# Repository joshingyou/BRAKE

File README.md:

# BRAKE
Introducing BRAKE: an integrated safety system designed for everyday bikers.

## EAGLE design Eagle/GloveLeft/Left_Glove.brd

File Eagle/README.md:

# BRAKE/Eagle
This is where the Eagle PCB design files live.

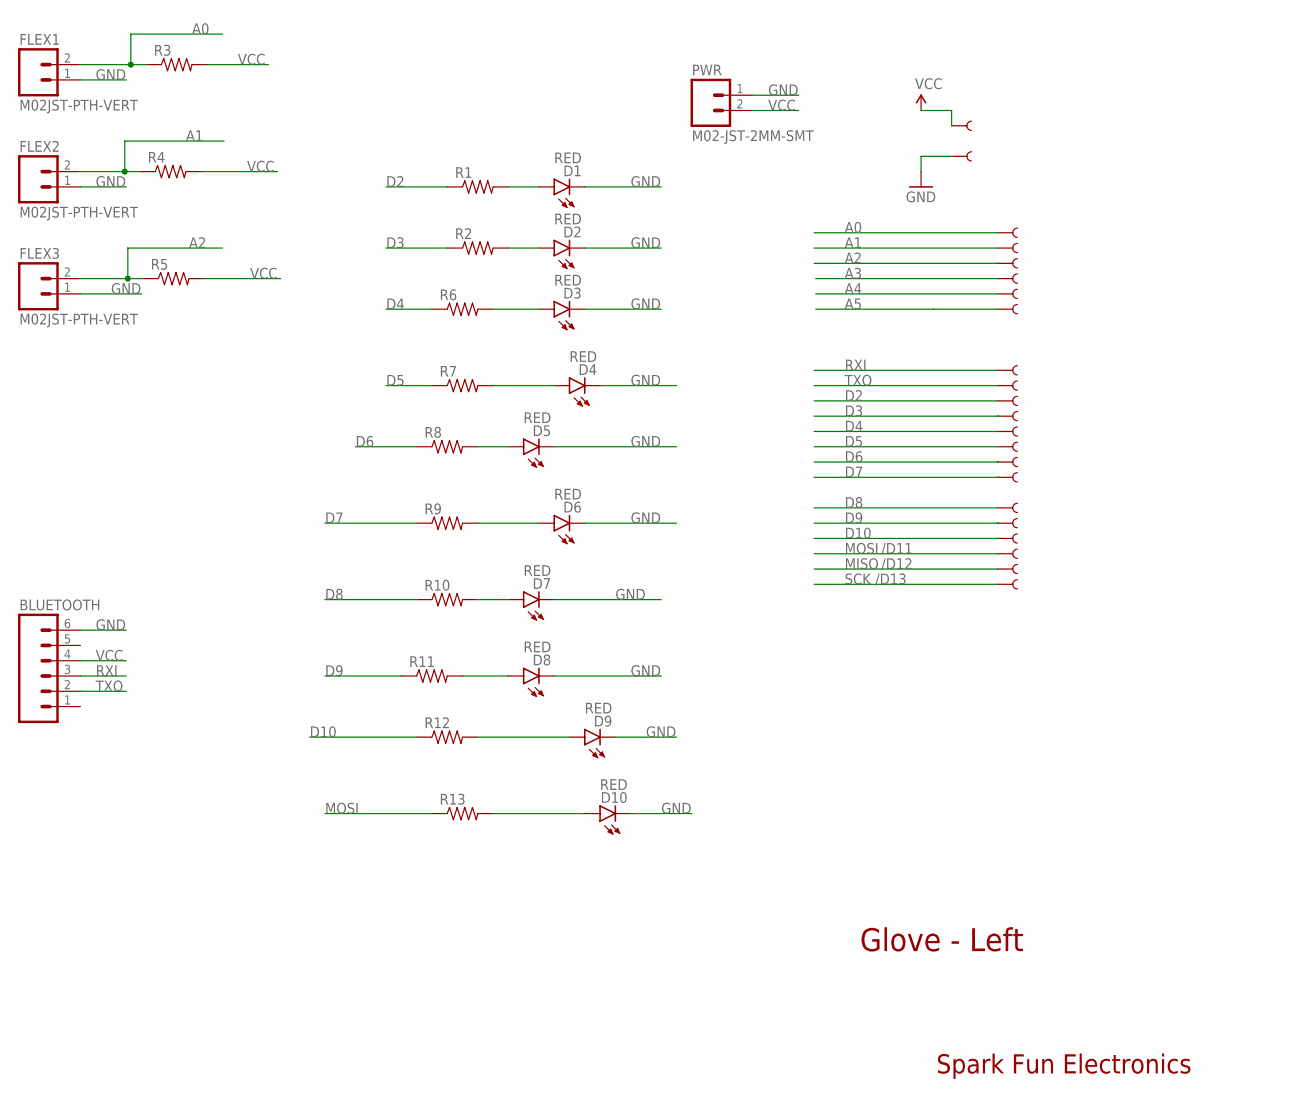
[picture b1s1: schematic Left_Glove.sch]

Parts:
BLUETOOTH: M06LOCK; 1X06_LOCK
D1, D2, D3, D4, D5, D6, D7, D8, D9, D10: RED; LED-1206
FLEX1, FLEX2, FLEX3: M02JST-PTH-VERT; JST-2-PTH-VERT
PWR: M02-JST-2MM-SMT; JST-2-SMD
R1, R2, R3, R4, R5, R6, R7, R8, R9, R10, R11, R12, R13: RESISTOR1206; 1206
U$22, U$23, U$24, U$26, U$27, U$28, U$29, U$30, U$31, U$32, U$33, U$34, U$35, U$36, U$37, U$38, U$39, U$40, U$41, U$42, U$43, U$44: SEWTAP1; PETAL-LONG-1

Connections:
A0: FLEX1.2, R3.1, U$24.P$1
A1: FLEX2.2, R4.1, U$26.P$1
A2: FLEX3.2, R5.1, U$27.P$1
A3: U$28.P$1
A4: U$29.P$1
A5: U$30.P$1
D2: R1.1, U$33.P$1
D3: R2.1, U$34.P$1
D4: R6.1, U$35.P$1
D5: R7.1, U$36.P$1
D6: R8.1, U$37.P$1
D7: R9.1, U$38.P$1
D8: R10.1, U$39.P$1
D9: R11.1, U$40.P$1
D10: R12.1, U$41.P$1
GND: BLUETOOTH.6, D1.C, D2.C, D3.C, D4.C, D5.C, D6.C, D7.C, D8.C, D9.C, D10.C, FLEX1.1, FLEX2.1, FLEX3.1, PWR.1 (2), U$23.P$1
MISO: U$43.P$1
MOSI: R13.1, U$42.P$1
unnamed: D10.A, R13.2
unnamed: D2.A, R2.2
unnamed: D1.A, R1.2
unnamed: D3.A, R6.2
unnamed: D4.A, R7.2
unnamed: D5.A, R8.2
unnamed: D6.A, R9.2
unnamed: D7.A, R10.2
unnamed: D8.A, R11.2
unnamed: D9.A, R12.2
RXI: BLUETOOTH.3, U$31.P$1
SCK: U$44.P$1
TXO: BLUETOOTH.2, U$32.P$1
VCC: BLUETOOTH.4, PWR.2 (1), R3.2, R4.2, R5.2, U$22.P$1

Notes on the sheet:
Glove - Left
Spark Fun Electronics
/D11
/D12
/D13

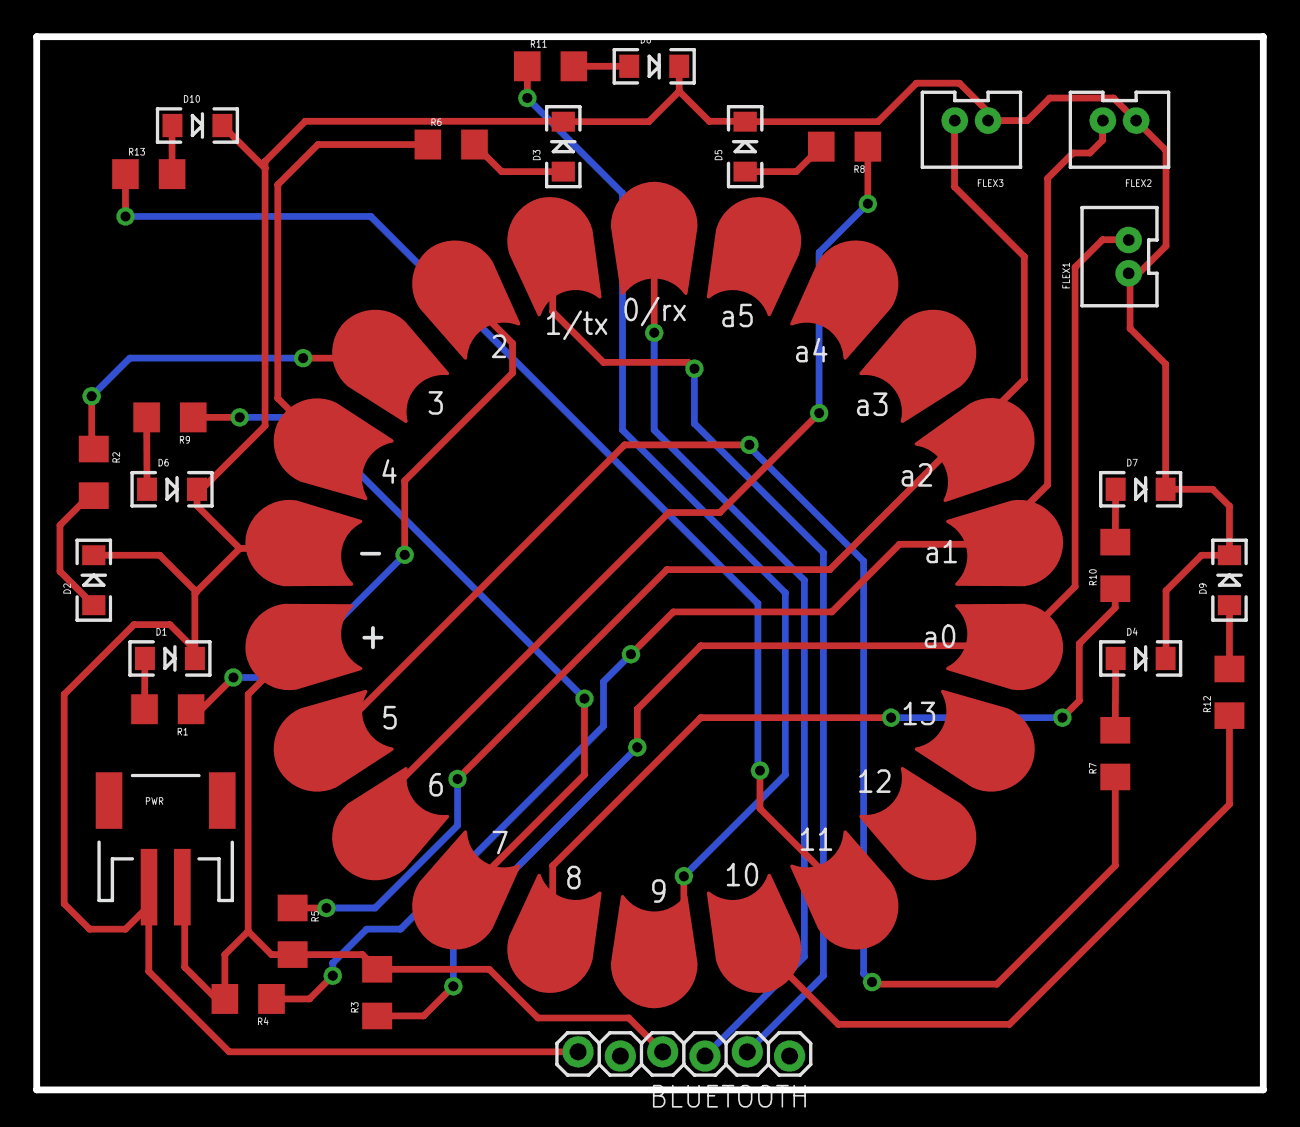
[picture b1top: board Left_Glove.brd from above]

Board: 2 copper layers, 73.7 x 63.2 mm, 50 parts (0 on the bottom side), 27 nets.

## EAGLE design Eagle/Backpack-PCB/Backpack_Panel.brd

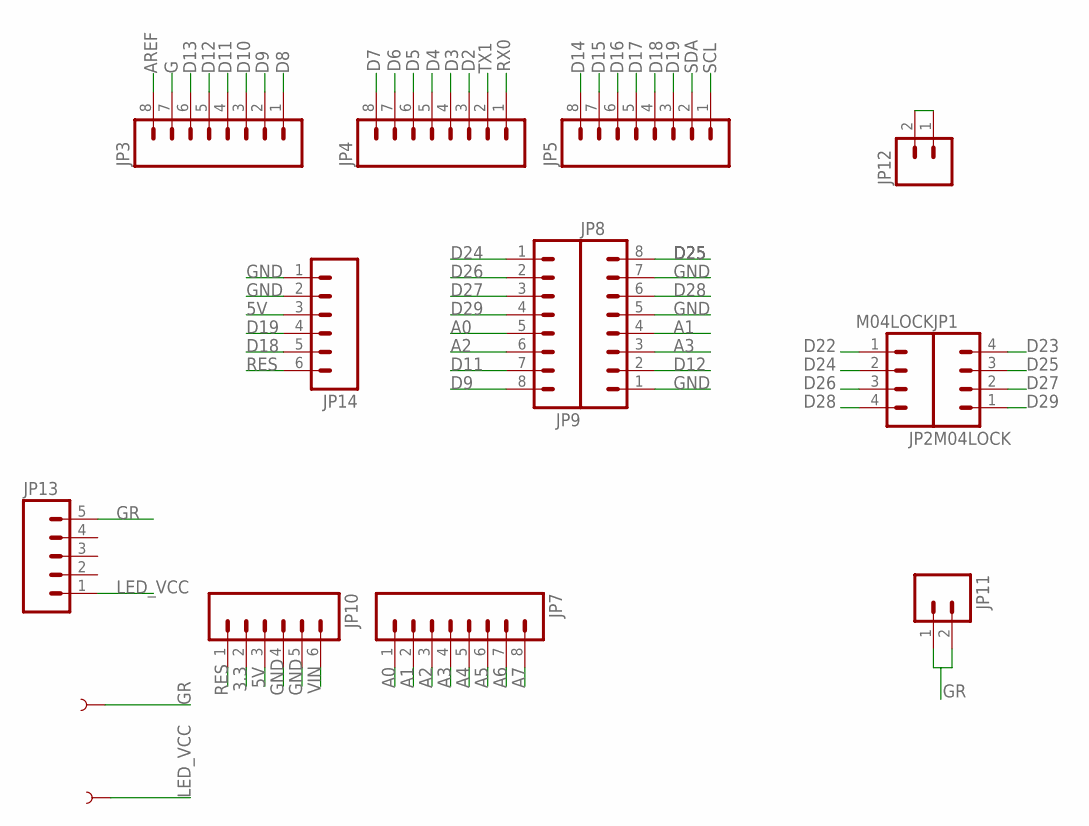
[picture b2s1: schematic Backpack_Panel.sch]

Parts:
JP1, JP2: M04LOCK; 1X04_LOCK
JP3, JP4, JP5, JP7, JP8, JP9: M08LOCK; 1X08_LOCK
JP10, JP14: M06LOCK; 1X06_LOCK
JP11, JP12: M02LOCK; 1X02_LOCK
JP13: M05LOCK; 1X05_LOCK
U$1, U$2: SEWTAP2; PETAL-LONG-2

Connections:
3.3: JP10.2
5V: JP10.3, JP14.3
A0: JP7.1, JP9.5
A1: JP7.2, JP8.4
A2: JP7.3, JP9.6
A3: JP7.4, JP8.3
A4: JP7.5
A5: JP7.6
A6: JP7.7
A7: JP7.8
AREF: JP3.8
D2: JP4.3
D3: JP4.4
D4: JP4.5
D5: JP4.6
D6: JP4.7
D7: JP4.8
D8: JP3.1
D9: JP3.2, JP9.8
D10: JP3.3
D11: JP3.4, JP9.7
D12: JP3.5, JP8.2
D13: JP3.6
D14: JP5.8
D15: JP5.7
D16: JP5.6
D17: JP5.5
D18: JP5.4, JP14.5
D19: JP5.3, JP14.4
D22: JP2.1
D23: JP1.4
D24: JP2.2, JP9.1
D25: JP1.3, JP8.8
D26: JP2.3, JP9.2
D27: JP1.2, JP9.3
D28: JP2.4, JP8.6
D29: JP1.1, JP9.4
G: JP3.7
GND: JP8.1, JP8.5, JP8.7, JP10.4, JP10.5, JP14.1, JP14.2
GR: JP11.1, JP11.2, JP13.5, U$1.1
LED_VCC: JP13.1, U$2.1
unnamed: JP12.1, JP12.2
RES: JP10.1, JP14.6
RX0: JP4.1
SCL: JP5.1
SDA: JP5.2
TX1: JP4.2
VIN: JP10.6

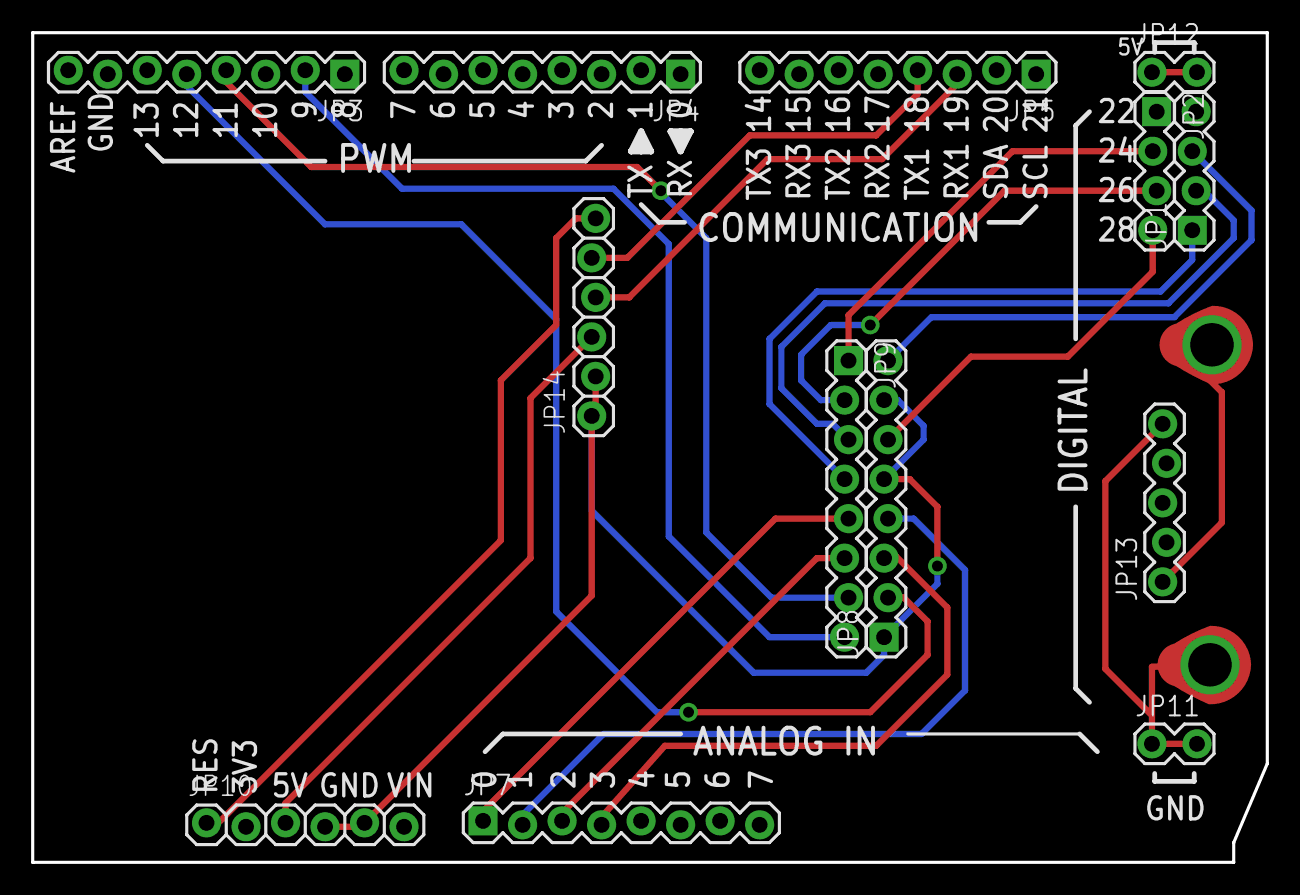
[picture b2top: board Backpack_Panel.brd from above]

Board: 2 copper layers, 79.4 x 53.3 mm, 15 parts (0 on the bottom side), 21 nets.

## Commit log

2015-02-23 Design proposal added
    Design proposal 1st draft that's submitted on Feb 12, 2015
2015-02-23 Created folders for different sub-systems
    Created folders for the Android app, the Arduino firmware and driver
    code, and Eagle PCB design files.
2015-03-18 SensorGloves C++ project was set up
    SensorGloves C++ project was set up
2015-03-18 Updated SensorGloves Atmel Studio project file
2015-03-30 python script and signaling gloves
2015-04-05 added android app
2015-04-05 removed app
2015-04-05 lab 3 code reference
2015-04-05 added app
2015-04-05 LED panel code so far
2015-04-05 arduino libraries
2015-04-06 Updated Backpack Arduino code and added Gloves arduino code (NOT TESTED)
    1. Added code that enables backpack arduino as Bluetooth Central and
    gloves arduino as Bluetooth Peripheral.
    2. Backpack should search for peripherals and connect to them.
    3. Once connected, backpack would send a special string "18549Team16"
    over and
    the glove would light up the onboard LED.
2015-04-06 Attempted bug fixes for arduino code
    Communication only works from central to peripheral but not the other
    way.
2015-04-08 Organized code in different sub functions.
    Also deleted unnecessary code.
2015-04-12 Created new Atmel Studio project for backpack led
    Also updated gitignore file to ignore DS_Store files
2015-04-14 Testing the basic environment setup. Keep giving me the error timeout
2015-04-15 added Sensor reading code and mapping.
2015-04-15 code for tap detection.. needs hardware testing
2015-04-20 Automatic calibration
2015-04-20 updated gesture code
2015-04-20 fixed the map bug
2015-04-26 Updated most code in C/C++ outside of Arduino IDE
    SensorGloves and BackpackLED both compile. Need to add code related to
    different packets coming in and out. Need to add interrupts.
2015-04-27 gloves messaging logic
2015-04-27 Fixed init().
    Added main.cpp so that we can write setup() and loop() functions like
    Arduino
2015-04-27 Added multi-tasking code
2015-04-28 Messed with Serial code. Doesn't work...
2015-04-29 Bluetooth works on a simple if statement now
2015-04-29 Backpack and sensor gloves bluetooth working.
    Need to work on sending ack back.
2015-04-29 Bluetooth works (sporadically)
    Again need to do ack stuff
2015-05-03 Relatively stable arduino code. Can send and receive from phone and backpack

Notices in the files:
parts and their libraries:
SparkFun-Connectors: Licensing: Creative Commons ShareAlike 4.0 International - https://creativecommons.org/licenses/by-sa/4.0
